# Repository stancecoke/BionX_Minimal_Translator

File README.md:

# BionX_Minimal_Translator

Run a BionX Motor with a Kunteng LCD-Display  

[Discussion in german forum](https://www.pedelecforum.de/forum/index.php?threads/bmt-bionx-motor-mit-no-name-akku-und-kunteng-display-betreiben.79599/post-1493208)  
["Bluepill" STM32F103 Board](https://rover.ebay.com/rover/1/707-53477-19255-0/1?ff3=4&pub=5575579753&toolid=10001&campid=5338673737&customid=post&mpre=https%3A%2F%2Fwww.ebay.de%2Fitm%2FSTM32F103C8T6-ARM-STM32-Minimum-System-Development-Board-Module-For-Arduino-MO%2F152246242164%3Fepid%3D16026102336%26hash%3Ditem2372954b74%3Ag%3AsE8AAOSwdjdaQh9o)  
[CAN-Driver-Board](https://rover.ebay.com/rover/1/707-53477-19255-0/1?ff3=4&pub=5575579753&toolid=10001&campid=5338673737&customid=post&mpre=https%3A%2F%2Fwww.ebay.de%2Fitm%2FNEW-MCP2551-High-Speed-CAN-Communicate-Protocol-Controller-Bus-Interface-Module%2F401132415647%3Fhash%3Ditem5d655aea9f%3Ag%3AEIYAAOSw6D1a9QN2)  
[Step Down Converter 12V + 5V](https://rover.ebay.com/rover/1/707-53477-19255-0/1?ff3=4&pub=5575579753&toolid=10001&campid=5338673737&customid=post&mpre=https%3A%2F%2Fwww.ebay.de%2Fitm%2FDC-DC-Buck-Step-Down-Converter-Power-Supply-Module-3-3V-5V-9V-12V-2A-600mA-AHS%2F302967906469%3FssPageName%3DSTRK%253AMEBIDX%253AIT%26_trksid%3Dp2057872.m2749.l2649)  
[Kunteng Display](https://rover.ebay.com/rover/1/707-53477-19255-0/1?ff3=4&pub=5575579753&toolid=10001&campid=5338673737&customid=post&mpre=https%3A%2F%2Fwww.ebay.de%2Fitm%2FEbike-Display-KT-Display-36V-48V-LCD3-LCD4-LCD5-LCD7-LCD8-LCD8H-LED880-LCD10H%2F373050638821%3Fhash%3Ditem56db8d01e5%3Am%3AmGUC02vhYdz2WcMOpRh0JzA)

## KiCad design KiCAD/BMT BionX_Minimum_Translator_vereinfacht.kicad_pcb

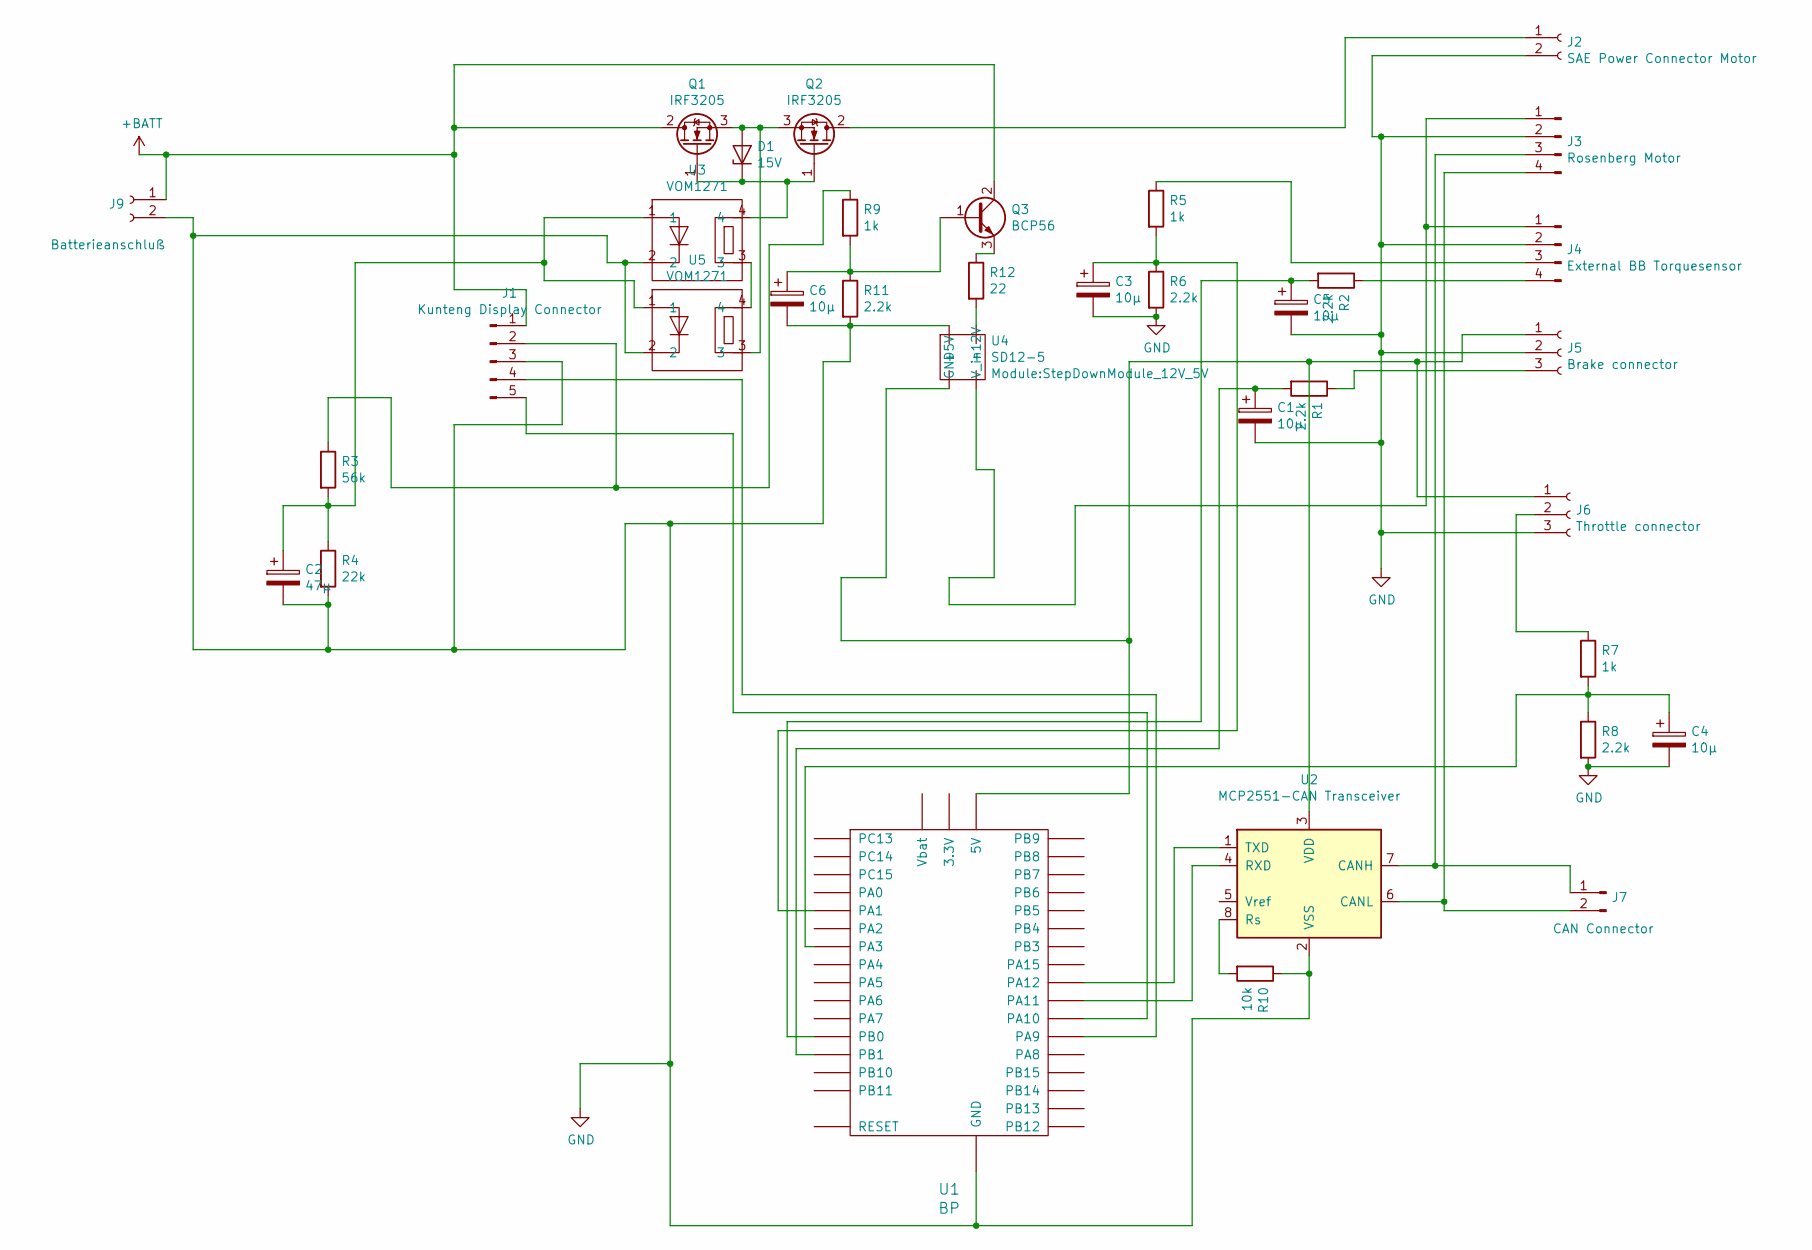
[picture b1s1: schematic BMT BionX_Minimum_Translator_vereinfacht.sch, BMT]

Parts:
C1, C3, C4, C5, C6: 10µ; CP_Radial_D5.0mm_P2.50mm
C2: 47µ; CP_Radial_D5.0mm_P2.50mm
D1: 15V; D_0805_2012Metric
J1: Kunteng Display Connector; JST_EH_B5B-EH-A_1x05_P2.50mm_Vertical
J2: SAE Power Connector Motor; Wago_734-132_1x02_P3.50mm_Vertical
J3: Rosenberg Motor; JST_EH_B4B-EH-A_1x04_P2.50mm_Vertical
J4: External BB Torquesensor; JST_EH_B4B-EH-A_1x04_P2.50mm_Vertical
J5: Brake connector; JST_EH_B3B-EH-A_1x03_P2.50mm_Vertical
J6: Throttle connector; JST_EH_B3B-EH-A_1x03_P2.50mm_Vertical
J7: CAN Connector; JST_EH_B2B-EH-A_1x02_P2.50mm_Vertical
J9: Batterieanschluß; Wago_734-132_1x02_P3.50mm_Vertical
Q1, Q2: IRF3205; TO-220-3_Vertical
Q3: BCP56; SOT-223
R1, R2, R6, R8, R11: 2.2k; R_0805_2012Metric
R3: 56k; R_0805_2012Metric
R4: 22k; R_0805_2012Metric
R5, R7, R9: 1k; R_0805_2012Metric
R10: 10k; R_0805_2012Metric
R12: 22; R_0805_2012Metric
U1: BP; BluePill
U2: MCP2551-CAN Transceiver; SOIC-8-1EP_3.9x4.9mm_P1.27mm_EP2.29x3mm
U3, U5: VOM1271; SOP-4_3.8x4.1mm_P2.54mm
U4: SD12-5; StepDownModule_12V_5V

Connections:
+BATT: J1.1, J9.1, Q1.2 (D), Q3.2 (C), Q3.4 (C)
GND: C1.2, C2.2, C3.2, C4.2, C5.2, C6.2, J1.3, J2.2, J3.2, J4.2, J5.2, J6.3, J9.2, R4.2, R6.2, R8.2, R10.1, R11.2, U1.GND, U2.2 (VSS), U3.2, U4.GND, U5.2; also elsewhere on the board
unnamed: C1.1, R1.2, U1.PB1
unnamed: C2.1, R3.2, R4.1, U3.1, U5.1
unnamed: C3.1, R5.2, R6.1, U1.PA1
unnamed: C4.1, R7.2, R8.1, U1.PA3
unnamed: C5.1, R2.2, U1.PB0
unnamed: C6.1, Q3.1 (B), R9.2, R11.1
unnamed 8: R12.2, U4.V_in; also elsewhere on the board
unnamed 9: J3.1, J4.1, U4.+12V; also elsewhere on the board
unnamed 10: J5.1, J6.1, U1.5V, U2.3 (VDD), U4.+5V; also elsewhere on the board
unnamed: D1.1 (K), Q1.1 (G), Q2.1 (G), U3.4
unnamed: D1.2 (A), Q1.3 (S), Q2.3 (S), U5.3
unnamed: J1.2, R3.1, R9.1
unnamed: J1.4, U1.PA9
unnamed: J1.5, U1.PA10
unnamed: J2.1, Q2.2 (D)
unnamed: J3.3, J7.1, U2.7 (CANH)
unnamed: J3.4, J7.2, U2.6 (CANL)
unnamed: J4.3, R5.1
unnamed: J4.4, R2.1
unnamed: J5.3, R1.1
unnamed: J6.2, R7.1
unnamed: Q3.3 (E), R12.1
unnamed: R10.2, U2.8 (Rs)
unnamed: U1.PA11, U2.4 (RXD)
unnamed: U1.PA12, U2.1 (TXD)
unnamed: U3.3, U5.4

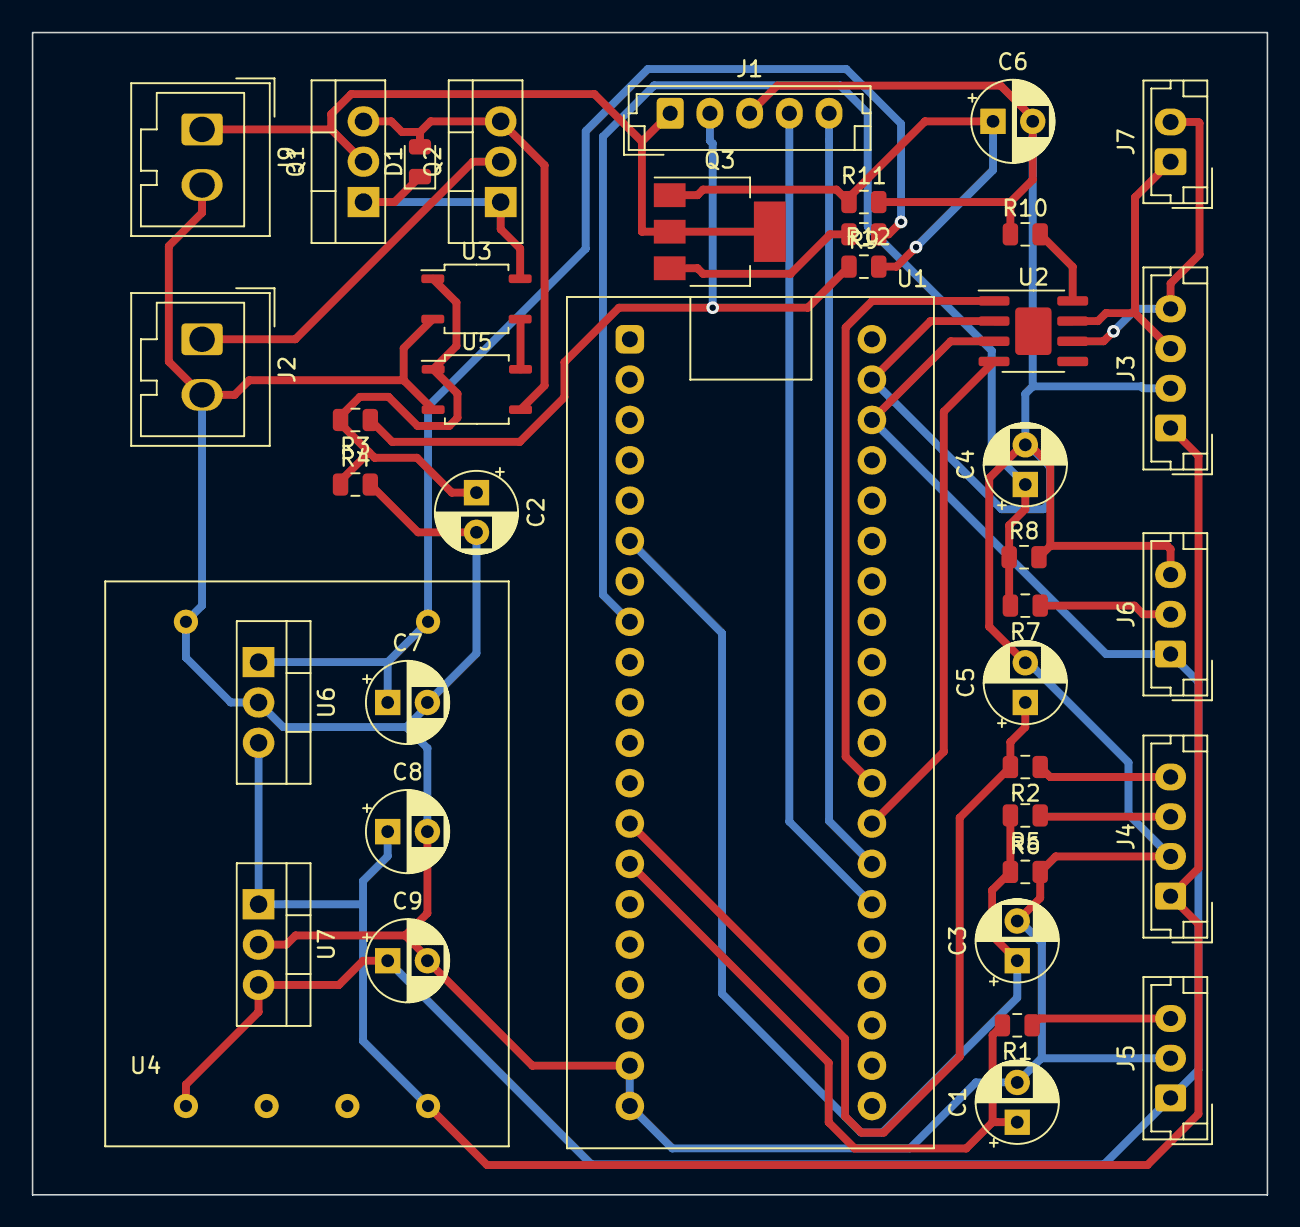
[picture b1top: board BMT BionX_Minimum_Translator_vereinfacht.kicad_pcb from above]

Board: 2 copper layers, 77.7 x 73.2 mm, 40 parts (0 on the bottom side), 28 nets.

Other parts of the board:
C7, C8, C9: 10µ; CP_Radial_D5.0mm_P2.50mm
U6: LM7812_TO220; TO-220-3_Vertical
U7: LM7805_TO220; TO-220-3_Vertical

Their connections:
GND: C7.2, C8.2, C9.2, U6.2, U7.2; also elsewhere on the board
unnamed 8: C7.1, U6.1; also elsewhere on the board
unnamed 9: C8.1, U6.3, U7.1; also elsewhere on the board
unnamed 10: C9.1, U7.3; also elsewhere on the board

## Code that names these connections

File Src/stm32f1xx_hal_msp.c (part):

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    __HAL_RCC_GPIOA_CLK_ENABLE();
    /**ADC1 GPIO Configuration
    PA0-WKUP     ------> ADC1_IN0
    PA1     ------> ADC1_IN1
    PA2     ------> ADC1_IN2
    */
    GPIO_InitStruct.Pin = GPIO_PIN_0|GPIO_PIN_1|GPIO_PIN_2|GPIO_PIN_3;
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
    /**ADC1 GPIO Configuration
    PA0-WKUP     ------> ADC1_IN0
    PA1     ------> ADC1_IN1
    PA2     ------> ADC1_IN2
    */
    HAL_GPIO_DeInit(GPIOA, GPIO_PIN_0|GPIO_PIN_1|GPIO_PIN_2);
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  
    __HAL_RCC_GPIOA_CLK_ENABLE();
    /**CAN GPIO Configuration    
    PA11     ------> CAN_RX
    PA12     ------> CAN_TX 
    */
    GPIO_InitStruct.Pin = GPIO_PIN_11;
    GPIO_InitStruct.Mode = GPIO_MODE_INPUT;
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    __HAL_RCC_CAN1_CLK_DISABLE();
  
    /**CAN GPIO Configuration    
    PA11     ------> CAN_RX
    PA12     ------> CAN_TX 
    */
    HAL_GPIO_DeInit(GPIOA, GPIO_PIN_11|GPIO_PIN_12);

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  
    __HAL_RCC_GPIOA_CLK_ENABLE();
    /**USART1 GPIO Configuration    
    PA9     ------> USART1_TX
    PA10     ------> USART1_RX 
    */
    GPIO_InitStruct.Pin = GPIO_PIN_9;
    GPIO_InitStruct.Mode = GPIO_MODE_AF_PP;
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    __HAL_RCC_USART1_CLK_DISABLE();
  
    /**USART1 GPIO Configuration    
    PA9     ------> USART1_TX
    PA10     ------> USART1_RX 
    */
    HAL_GPIO_DeInit(GPIOA, GPIO_PIN_9|GPIO_PIN_10);

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
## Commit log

2020-06-07 Create LICENSE
2020-06-16 libraries for Kunteng-Displays added.
2020-06-19 Links added to readme
2020-06-25 WIP for switch to latest HAL-version
2020-06-25 Switch to latest HAL-Driver
2020-06-26 BionX command with input from UART
2020-06-26 CAN initialisation updated
2020-06-27 Blink on PC13 for indication
2020-07-01 New approach with most recent HAL library
2020-07-01 Disable Ring Buffer for UART_TX, Reset UART before each send command
2020-07-02 Sent Can Message added
2020-07-02 Ask for software version at startup
2020-07-04 bugfix in CAN-handler naming
2020-07-05 wip - no valid CAN message so far :-(
2020-07-05 WIP CAN RX interrupt still not working
2020-07-06 CAN TX Interrupt working now
2020-07-07 Communication between to nodes working now :-)
2020-07-08 Linker file added
2020-07-13 Timing with timer3@1kHz, ADC with DMA
2020-07-14 CAN request as function
2020-07-24 Can Request and Can Command function improved
2020-07-25 hi-Byte and lo-Byte from UART
2020-07-26 Reading Gauge_Voltage from 0xC9(CA
2020-07-26 UART first byte 0 TorqueOut, 1 Command, 2 Request
2020-07-27 Auto-offset for DMS signal at startup.
2020-07-30 calculate current target and send it to motor controller
2020-07-30 Workaround for gauge_voltage resets
2020-07-31 KiCAD files added
2020-08-01 KiCAD: Switch on hi-side with BTS432
2020-08-01 bugfix in schematic
2020-08-01 again bugfix in schematic
2020-08-01 Zener diode at HiSide-Switch input added
2020-08-02 merged NewHAL branch to master with Kunteng libraries
2020-08-02 bugfix in pinout of BTS432
2020-08-02 display communicatin working now.
2020-08-02 WIP timer3 interrupt processing not reliable
2020-08-03 Can termination resistor added
2020-08-03 Bugfix for paranthesis in #ifs
2020-08-03 read Speed and Power via CAN from the motor
2020-08-03 Parameter P1 assigned to Gauge_Factor
2020-08-04 toggle led only if CAN TX ready
2020-08-04 CAN-Registers.h implemented
2020-08-04 sniffing function adapted
2020-08-04 send request in UART RX added
2020-08-04 REG_MOTOR_ASSIST_LEVEL added to output
2020-08-04 update KiCAD schematic
2020-08-04 Set UART BAUD rate to 115200
2020-08-04 CAN-Registers.h included and Debug-BAUD to 115200
2020-08-04 send only requested value und debug mode
2020-08-05 riders torque read from 0x21
2020-08-05 WIP implementig perma regen
2020-08-05 perma regen implemented
2020-08-05 Throttle added with override function for regen and power
2020-08-05 small changes
2020-08-06 support for external torque sensor, activated by parameter P3
2020-08-06 PAS timeout added
2020-08-06 voltage devider 5V -> 3.3v in schematic, adc-values print in debugmode
2020-08-08 bugfix in adc init
2020-08-08 capacitors on analog inputs added to schematic
2020-08-09 Power and Speed added to printout
2020-08-10 little update
2020-08-13 Dispaly Max Speed and Wheelsize settings sent to Motor if changed
2020-08-13 scaling of speed display corrected
2020-08-13 Slow loop CAN TX for less time critical paramters
2020-08-13 setting of serial battery cells with P2
2020-08-14 Kunteng Display-Test
2020-08-14 deleted unnecessary CAN-Requests
2020-08-15 only send UART Message, if answer from motor was received
2020-08-15 bugfix in debug mode
2020-08-16 Update of schematic with untested "Antiblitz"
2020-08-28 changed logged parameters
2020-08-29 WIP debugging external torquesensor function
2020-08-29 Success: assist with external torquesensor is working now.
2020-08-30 default value for Regen_Factor in debug mode
2020-08-31 Throttle function per P4, Battery max current per C2
2020-08-31 Merged last changes
2020-09-13 gauge voltage added to debug output
2020-09-15 default value for Throttle function added
2020-09-16 send current target only if battery voltage is high enough
2020-09-20 overvoltage protection @regen added
2020-09-26 Changed to PI control for keeping max voltage limit at regen.
2020-09-29 read GaugeValue in debug mode
2020-10-05 Filter and Gauge Gain implemented as C4 and C5 parameter
2020-10-05 timeout of gauge value added for legalizing of throttle
2020-10-05 bugfix in gauge timeout
2020-10-09 simplified schematic added
2020-10-09 PDF of schematic added
2020-10-11 Processor pinout added
2020-10-11 simplified schematic with VOM1271
2020-10-11 Pinout bugfix
2020-10-12 PCB layout with SMD: first try
2020-10-12 switched to 0805 Size
2020-10-12 schematic as pdf updated
2020-10-12 2 Layer routing
2020-10-12 schematic as PDF
2020-10-12 Step Down switched seperately
2020-10-14 separated voltage regulators as alternative added.
2020-11-07 added filter for speedsignal
2020-11-27 Bafang settings
2020-12-20 Try to emulate controller for Bafang Display communication
2020-12-22 further unsuccessful approach to emulate Controller
2020-12-22 New approach to be tested
2020-12-23 with message ID
2020-12-23 Messages analysed and implement as far as understood
2020-12-23 small update WIP
2020-12-23 Speed1 and Speed2
2020-12-23 Bugfix in CAN-Register
2020-12-23 CAN Commands in sequence
2020-12-23 Sync CAN Tx with CAN Rx
2020-12-24 shift every 150 messages
2020-12-24 32bit ExtID
2020-12-24 Update 32bit ExtID
2020-12-24 collect ExtIDs in Array
2020-12-25 Bugfix in ExtID only
2020-12-25 timeCounter added
2020-12-25 timing adjusted
2020-12-26 comment edited
2025-07-07 decode ext. frame ID
2025-07-08 print only long messages from app
2025-08-16 blink and send without UART
2026-02-14 Use as sniffer for debug frame 0x00010203

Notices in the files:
Src/stm32f1xx_hal_msp.c:
© Copyright (c) 2020 STMicroelectronics.
All rights reserved.
This software component is licensed by ST under BSD 3-Clause license,
the "License"; You may not use this file except in compliance with the
License. You may obtain a copy of the License at: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
(C) COPYRIGHT STMicroelectronics *****END OF FILE
